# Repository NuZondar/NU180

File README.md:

# NU180
A reverse-engineered replacement for the U180 hybrid in the Hewlett-Packard / Agilent / Keysight 3458A DVM. 

Briefly, the custom "U180" hybrid in the 3458A is infamously prone to excessive drifting or outright failure, but is absolutely unavailable. NU180 is a drop-in replacement for that hybrid. Still under development, its performance falls slightly short of an original U180, e.g. noise performance is ~20-30% higher than spec, but it thus provides at least 8 digits conversion (within 2x of 8.5 digits), which is infinitely better than a dead or dying machine! 

Some notes:

The new Version 1.1 files are denoted "v11" in their names. 

The layout requires 6 layers. Choose a thin stack-up - that is, thinner core layers - if available. 

Choose the best resistors you can find, especially for their TCR (temperature coefficient of resistance). In particular, the use of low TCR bulk-foil resistors for at least the 50k and most-critical 80k's are recommended for best temperature stability. 

The footprints for the critical 80k's allow choosing either large 2512 surface-mount resistors, or else through-hole resistors (same for the 50k). These are intended for builders who are using bulk-foil resistors (80k's only come in 2512 size). You can edit the files to delete the unused footprints or else leave them in place. Another option for the 50k and 80k resistors is to edit the files to substitute a small array of series or parallel resistors. There's room for up to 4 each, e.g. 4x 20k in series for the 80k's, etc. 

You also have the option of using voltage regulation on the flip-flop and inverter (recommended), or else using unregulated 5V, chosen via jumpers. The schematic shows parts suitable for 3.3V operation, but other parts may allow operation down to 2.5V. The lower-voltage regulation should help keep noise down. 

The 100k resistors to ground are optional and need not be included unless some problem is seen. 

Debugging: The 3458A is a very sensitive instrument that can be quite fussy about error codes. At least in earlier versions, builders have sometimes found that changing the value of the series resistors (the 100 Ohm ones) up or down, e.g. to 33 or 220 Ohms, can help. Usually, only the four switch control lines associated with the 80k resistors (S5, S7, S9, S11) might need tuning. Another hack that has sometimes helped is adding a small capacitor (5-10 pF) in parallel with the R140 resistor on the A3 board.

There is extensive discussion of this project in the metrology section of EEVblog. Many people contributed their knowledge and experience towards its success, including MiDi, DB4UCH, wanghar, Kleinstein and others. 

Good luck!

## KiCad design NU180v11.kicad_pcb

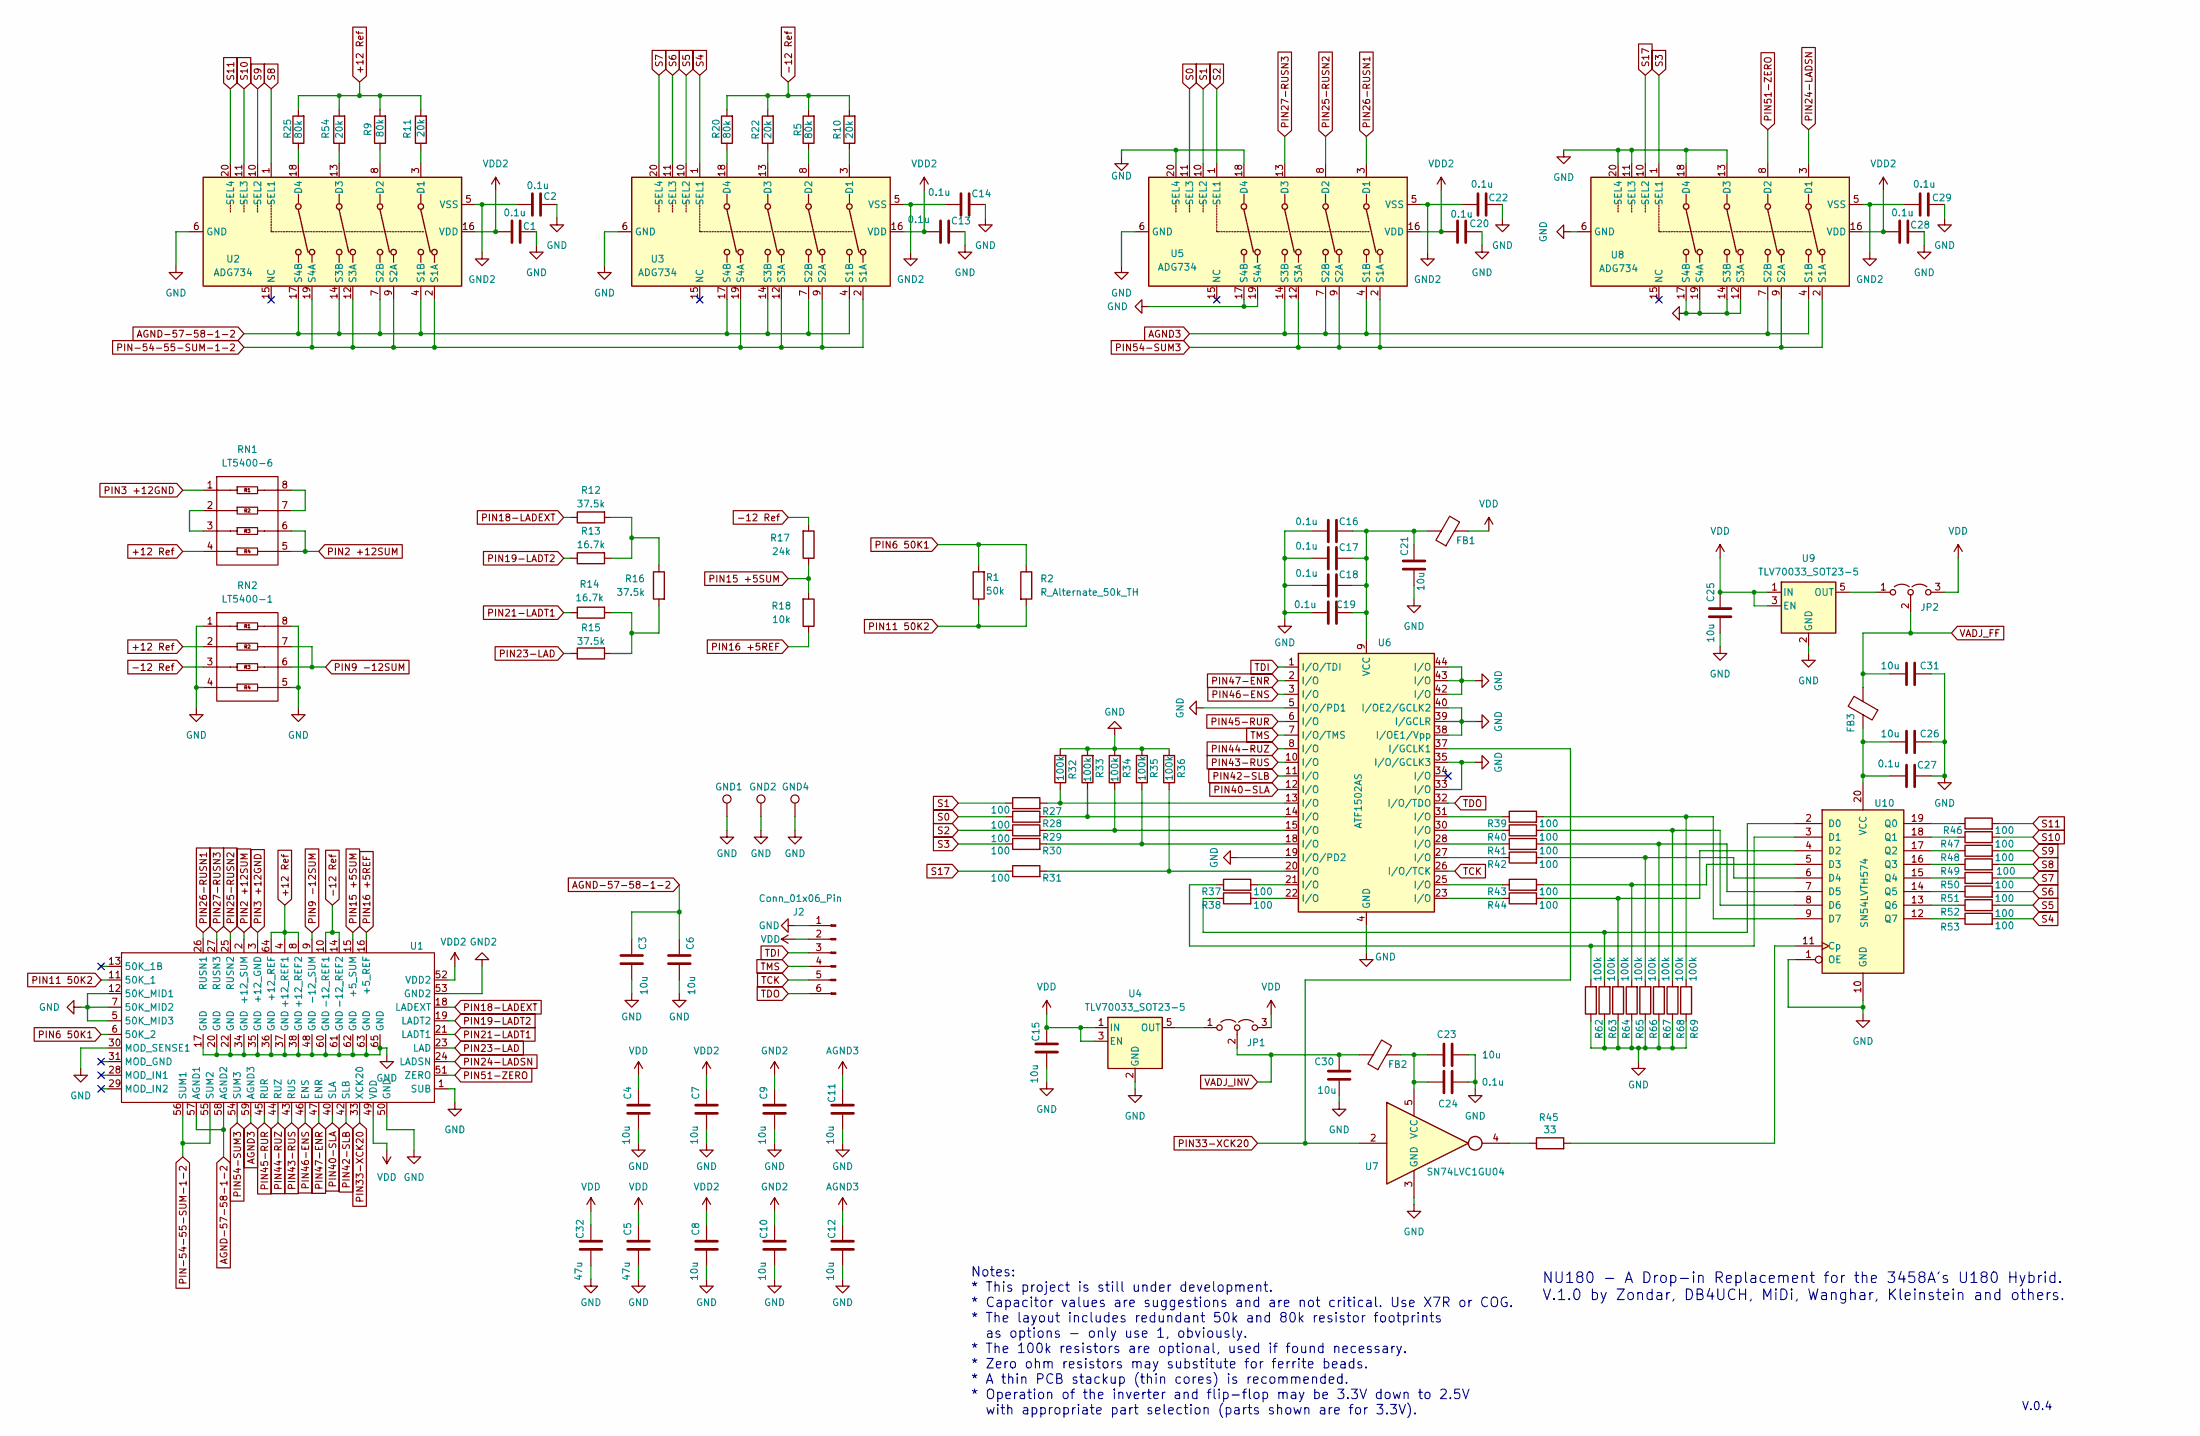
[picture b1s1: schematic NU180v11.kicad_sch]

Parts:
C1, C2, C13, C14, C16, C17, C18, C19, C20, C22, C24, C27, C28, C29: 0.1u; C_0603_1608Metric
C3, C4, C6, C7, C8, C9, C10, C11, C12, C15, C21, C23, C25, C26, C30, C31: 10u; C_0805_2012Metric_Pad1.18x1.45mm_HandSolder
C5, C32: 47u; C_1206_3216Metric
FB1, FB2, FB3: Ferrite Bead or Short; C_0603_1608Metric
GND1, GND2, GND4: TestPoint; PinHeader_1x01_P2.54mm_Vertical
J2: Conn_01x06_Pin; PinHeader_1x06_P2.54mm_Vertical
JP1, JP2: Jumper_3_Open; SolderJumper-3_P2.0mm_Open_TrianglePad1.0x1.5mm
R1: 50k; R_2010_5025Metric
R2: R_Alternate_50k_TH; R_Axial_DIN0204_L3.6mm_D1.6mm_P5.08mm_Horizontal
R5, R9, R20, R25: 80k; R_2512_6332Metric
R10, R11, R22, R54: 20k; R_1206_3216Metric
R12, R15, R16: 37.5k; R_0805_2012Metric
R13, R14: 16.7k; R_0805_2012Metric
R17: 24k; R_1206_3216Metric
R18: 10k; R_1206_3216Metric
R27, R28, R29, R30, R31, R37, R38, R39, R40, R41, R42, R43, R44, R46, R47, R48, R49, R50, R51, R52, R53: 100; R_0603_1608Metric
R32, R33, R34, R35, R36, R62, R63, R64, R65, R66, R67, R68, R69: 100k; R_0603_1608Metric
R45: 33; R_0603_1608Metric
RN1: LT5400-6; MSOP-8-1EP_3x3mm_P0.65mm_EP1.68x1.88mm
RN2: LT5400-1; MSOP-8-1EP_3x3mm_P0.65mm_EP1.68x1.88mm
U1: U180PINS
U2, U3, U5, U8: ADG734; TSSOP-20_4.4x6.5mm_P0.65mm
U4, U9: TLV70033_SOT23-5; SOT-23-5
U6: ATF1502AS; TQFP-44_10x10mm_P0.8mm
U7: SN74LVC1GU04; SOT-353_SC-70-5
U10: SN54LVTH574; TSSOP-20_4.4x6.5mm_P0.65mm

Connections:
+12 Ref: R9.2, R11.2, R25.2, R54.2, RN1.4, RN2.2, U1.4 (+12_REF1), U1.8 (+12_REF2), U1.64 (+12_REF)
-12 Ref: R5.2, R10.2, R17.2, R20.2, R22.2, RN2.3, U1.10 (-12_REF1), U1.14 (-12_REF2)
AGND3: C11.2, C12.2, U1.59 (AGND3), U5.4 (S1B), U5.7 (S2B), U5.14 (S3B), U8.4 (S1B), U8.7 (S2B)
AGND-57-58-1-2: C3.2, C6.2, U1.57 (AGND1), U1.58 (AGND2), U2.4 (S1B), U2.7 (S2B), U2.14 (S3B), U2.17 (S4B), U3.4 (S1B), U3.7 (S2B), U3.14 (S3B), U3.17 (S4B)
GND: C1.2, C2.2, C3.1, C4.1, C5.1, C6.1, C7.1, C8.1, C9.1, C10.1, C11.1, C12.1, C13.2, C14.2, C15.1, C16.1, C17.1, C18.1, C19.1, C20.2, C21.1, C22.2, C23.2, C24.2, C25.1, C26.2, C27.2, C28.2, C29.2, C30.1, C31.2, C32.1, GND1.1, GND2.1, GND4.1, J2.1, R32.2, R33.2, R34.2, R35.2, R36.2, R62.1, R63.1, R64.1, R65.1, R66.1, R67.1, R68.1, R69.1, RN2.1, RN2.4, RN2.5, RN2.8, U1.1 (SUB), U1.5 (50K_MID3), U1.7 (50K_MID2), U1.12 (50K_MID1), U1.17 (GND), U1.20 (GND), U1.22 (GND), U1.30 (MOD_SENSE1), U1.34 (GND), U1.35 (GND), U1.36 (GND), U1.37 (GND), U1.38 (GND), U1.48 (GND), U1.50 (GND), U1.60 (GND), U1.61 (GND), U1.62 (GND), U1.63 (GND), U1.65 (GND), U2.6 (GND), U3.6 (GND), U4.2 (GND), U5.6 (GND), U5.17 (S4B), U5.18 (D4), U5.19 (S4A), U5.20 (SEL4), U6.4 (GND), U6.5 (I/O/PD1), U6.16 (GND), U6.19 (I/O/PD2), U6.24 (GND), U6.33 (I/O), U6.35 (I/O/GCLK3), U6.36 (GND), U6.38 (I/OE1/Vpp), U6.39 (I/GCLR), U6.40 (I/OE2/GCLK2), U6.42 (I/O), U6.43 (I/O), U6.44 (I/O), U7.3 (GND), U8.6 (GND), U8.11 (SEL3), U8.12 (S3A), U8.13 (D3), U8.14 (S3B), U8.17 (S4B), U8.18 (D4), U8.19 (S4A), U8.20 (SEL4), U9.2 (GND), U10.1 (OE), U10.10 (GND); also elsewhere on the board
GND2: C2.1, C9.2, C10.2, C14.1, C22.1, C29.1, U1.53 (GND2), U2.5 (VSS), U3.5 (VSS), U5.5 (VSS), U8.5 (VSS)
unnamed: C16.2, C17.2, C18.2, C19.2, C21.2, FB1.1, U6.9 (VCC), U6.17 (VCC), U6.29 (VCC), U6.41 (VCC)
unnamed: JP1.1 (A), U4.5 (OUT)
unnamed: JP2.1 (A), U9.5 (OUT)
unnamed: R12.2, R13.2, R16.1
unnamed: R14.2, R15.2, R16.2
unnamed: R27.2, R32.1, U6.13 (I/O)
unnamed: R28.2, R33.1, U6.14 (I/O)
unnamed: R29.2, R34.1, U6.15 (I/O)
unnamed: R30.2, R35.1, U6.18 (I/O)
unnamed: R31.2, R36.1, U6.20 (I/O)
unnamed: R37.2, U6.21 (I/O)
unnamed: R38.2, U6.22 (I/O)
unnamed: R39.1, U6.31 (I/O)
unnamed: R40.1, U6.30 (I/O)
unnamed: R41.1, U6.28 (I/O)
unnamed: R42.1, U6.27 (I/O)
unnamed: R43.1, U6.25 (I/O)
unnamed: R44.1, U6.23 (I/O)
unnamed: R45.1, U7.4
unnamed: RN1.2, RN1.3
unnamed: RN1.7, RN1.8
unnamed: R11.1, U2.3 (D1)
unnamed: R9.1, U2.8 (D2)
unnamed: R54.1, U2.13 (D3)
unnamed: R25.1, U2.18 (D4)
unnamed: R10.1, U3.3 (D1)
unnamed: R5.1, U3.8 (D2)
unnamed: R22.1, U3.13 (D3)
unnamed: R20.1, U3.18 (D4)
unnamed: C23.1, C24.1, FB2.2, U7.5 (VCC)
unnamed: R45.2, U10.11 (Cp)
unnamed: R38.1, R63.2, U10.2 (D0)
unnamed: R37.1, R62.2, U10.3 (D1)
unnamed: R44.2, R64.2, U10.4 (D2)
unnamed: R43.2, R65.2, U10.5 (D3)
unnamed: R42.2, R66.2, U10.6 (D4)
unnamed: R41.2, R67.2, U10.7 (D5)
unnamed: R40.2, R68.2, U10.8 (D6)
unnamed: R39.2, R69.2, U10.9 (D7)
unnamed: R46.1, U10.19 (Q0)
unnamed: R47.1, U10.18 (Q1)
unnamed: R48.1, U10.17 (Q2)
unnamed: R49.1, U10.16 (Q3)
unnamed: R50.1, U10.15 (Q4)
unnamed: R51.1, U10.14 (Q5)
unnamed: R52.1, U10.13 (Q6)
unnamed: R53.1, U10.12 (Q7)
unnamed: C26.1, C27.1, FB3.1, U10.20 (VCC)
PIN2 +12SUM: RN1.5, RN1.6, U1.2 (+12_SUM)
PIN3 +12GND: RN1.1, U1.3 (+12_GND)
PIN6 50K1: R1.2, R2.1, U1.6 (50K_2)
PIN9 -12SUM: RN2.6, RN2.7, U1.9 (-12_SUM)
PIN11 50K2: R1.1, R2.2, U1.11 (50K_1)
PIN15 +5SUM: R17.1, R18.2, U1.15 (+5_SUM)
PIN16 +5REF: R18.1, U1.16 (+5_REF)
PIN18-LADEXT: R12.1, U1.18 (LADEXT)
PIN19-LADT2: R13.1, U1.19 (LADT2)
PIN21-LADT1: R14.1, U1.21 (LADT1)
PIN23-LAD: R15.1, U1.23 (LAD)
PIN24-LADSN: U1.24 (LADSN), U8.3 (D1)
PIN25-RUSN2: U1.25 (RUSN2), U5.8 (D2)
PIN26-RUSN1: U1.26 (RUSN1), U5.3 (D1)
PIN27-RUSN3: U1.27 (RUSN3), U5.13 (D3)
PIN33-XCK20: U1.33 (XCK20), U6.37 (I/GCLK1), U7.2
PIN40-SLA: U1.40 (SLA), U6.12 (I/O)
PIN42-SLB: U1.42 (SLB), U6.11 (I/O)
PIN43-RUS: U1.43 (RUS), U6.10 (I/O)
PIN44-RUZ: U1.44 (RUZ), U6.8 (I/O)
PIN45-RUR: U1.45 (RUR), U6.6 (I/O)
PIN46-ENS: U1.46 (ENS), U6.3 (I/O)
PIN47-ENR: U1.47 (ENR), U6.2 (I/O)
PIN51-ZERO: U1.51 (ZERO), U8.8 (D2)
PIN54-SUM3: U1.54 (SUM3), U5.2 (S1A), U5.9 (S2A), U5.12 (S3A), U8.2 (S1A), U8.9 (S2A)
PIN-54-55-SUM-1-2: U1.55 (SUM2), U1.56 (SUM1), U2.2 (S1A), U2.9 (S2A), U2.12 (S3A), U2.19 (S4A), U3.2 (S1A), U3.9 (S2A), U3.12 (S3A), U3.19 (S4A)
S0: R28.1, U5.11 (SEL3)
S1: R27.1, U5.10 (SEL2)
S2: R29.1, U5.1 (SEL1)
S3: R30.1, U8.1 (SEL1)
S4: R53.2, U3.1 (SEL1)
S5: R52.2, U3.10 (SEL2)
S6: R51.2, U3.11 (SEL3)
S7: R50.2, U3.20 (SEL4)
S8: R49.2, U2.1 (SEL1)
S9: R48.2, U2.10 (SEL2)
S10: R47.2, U2.11 (SEL3)
S11: R46.2, U2.20 (SEL4)
S17: R31.1, U8.10 (SEL2)
TCK: J2.5, U6.26 (I/O/TCK)
TDI: J2.3, U6.1 (I/O/TDI)
TDO: J2.6, U6.32 (I/O/TDO)
TMS: J2.4, U6.7 (I/O/TMS)
VADJ_FF: C31.1, FB3.2, JP2.2 (C)
VADJ_INV: C30.2, FB2.1, JP1.2 (C)
VDD: C4.2, C5.2, C15.2, C25.2, C32.2, FB1.2, J2.2, JP1.3 (B), JP2.3 (B), U1.49 (VDD), U4.1 (IN), U4.3 (EN), U9.1 (IN), U9.3 (EN)
VDD2: C1.1, C7.2, C8.2, C13.1, C20.1, C28.1, U1.52 (VDD2), U2.16 (VDD), U3.16 (VDD), U5.16 (VDD), U8.16 (VDD)

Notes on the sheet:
V.0.4
Notes: * This project is still under development. * Capacitor values are suggestions and are not critical. Use X7R or COG. * The layout includes redundant 50k and 80k resistor footprints as options - only use 1, obviously. * The 100k resistors are optional, used if found necessary. * Zero ohm resis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
NU180 - A Drop-in Replacement for the 3458A's U180 Hybrid. V.1.0 by Zondar, DB4UCH, MiDi, Wanghar, Kleinstein and others.

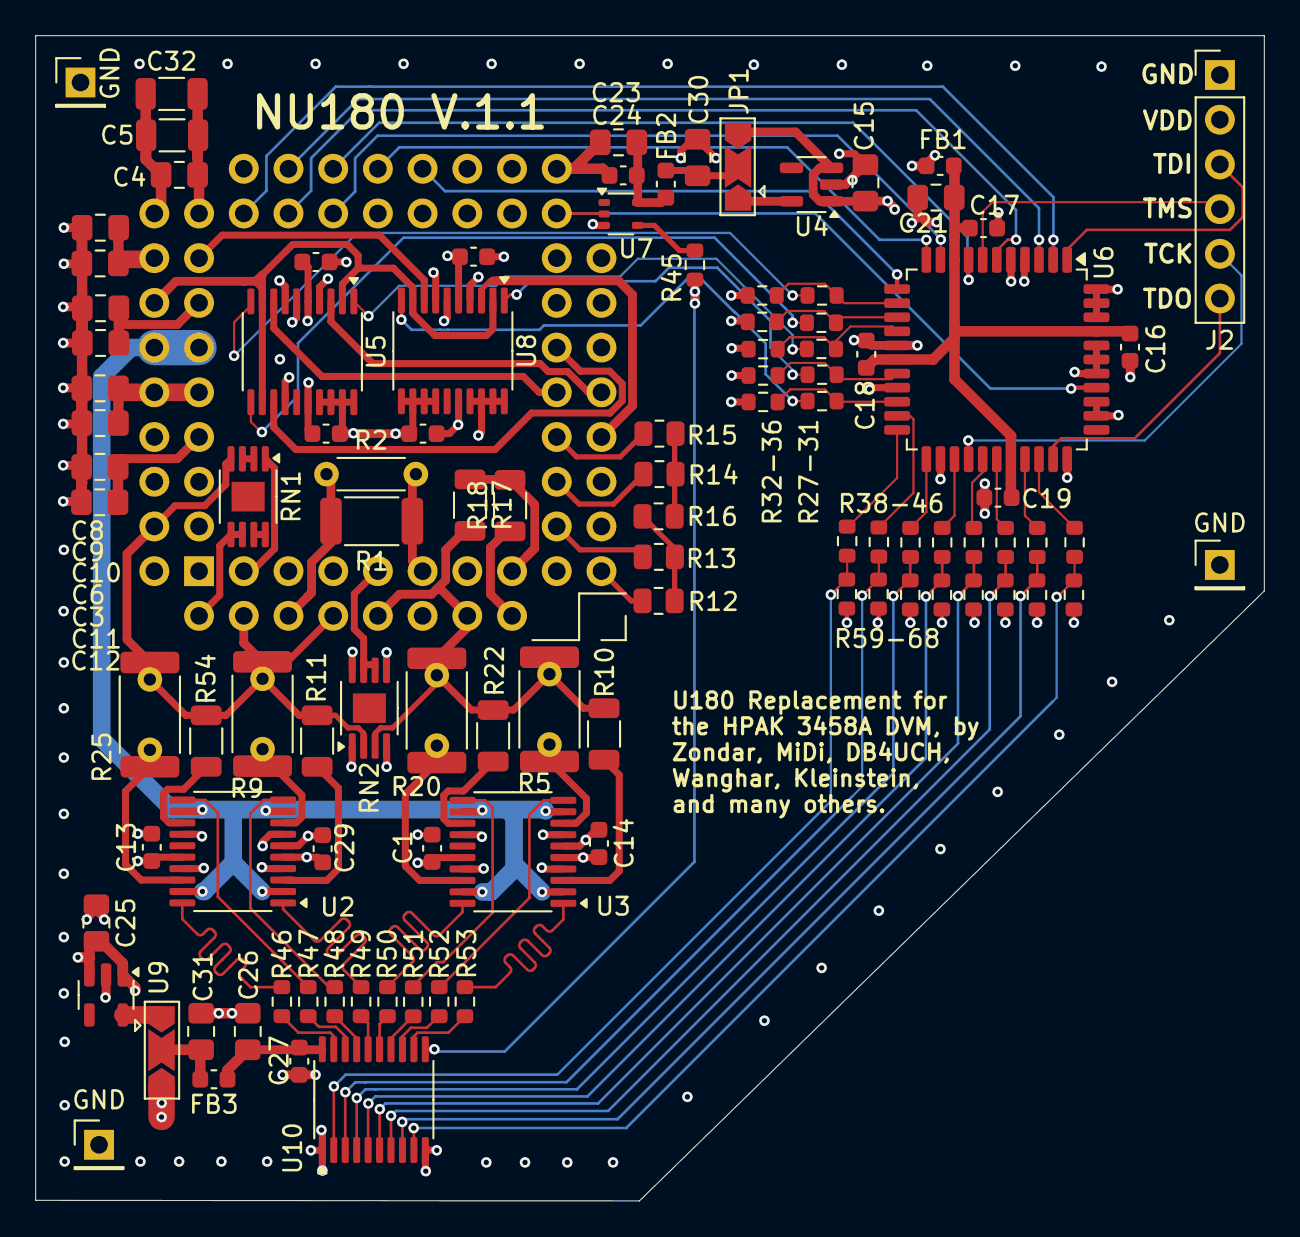
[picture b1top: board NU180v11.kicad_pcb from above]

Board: 6 copper layers, 69.8 x 66.2 mm, 105 parts (0 on the bottom side), 101 nets.

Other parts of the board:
GND: TestPoint; PinHeader_1x01_P2.54mm_Vertical
GND#2: TestPoint; PinHeader_1x01_P2.54mm_Vertical

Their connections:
GND: GND.1, GND#2.1; also elsewhere on the board

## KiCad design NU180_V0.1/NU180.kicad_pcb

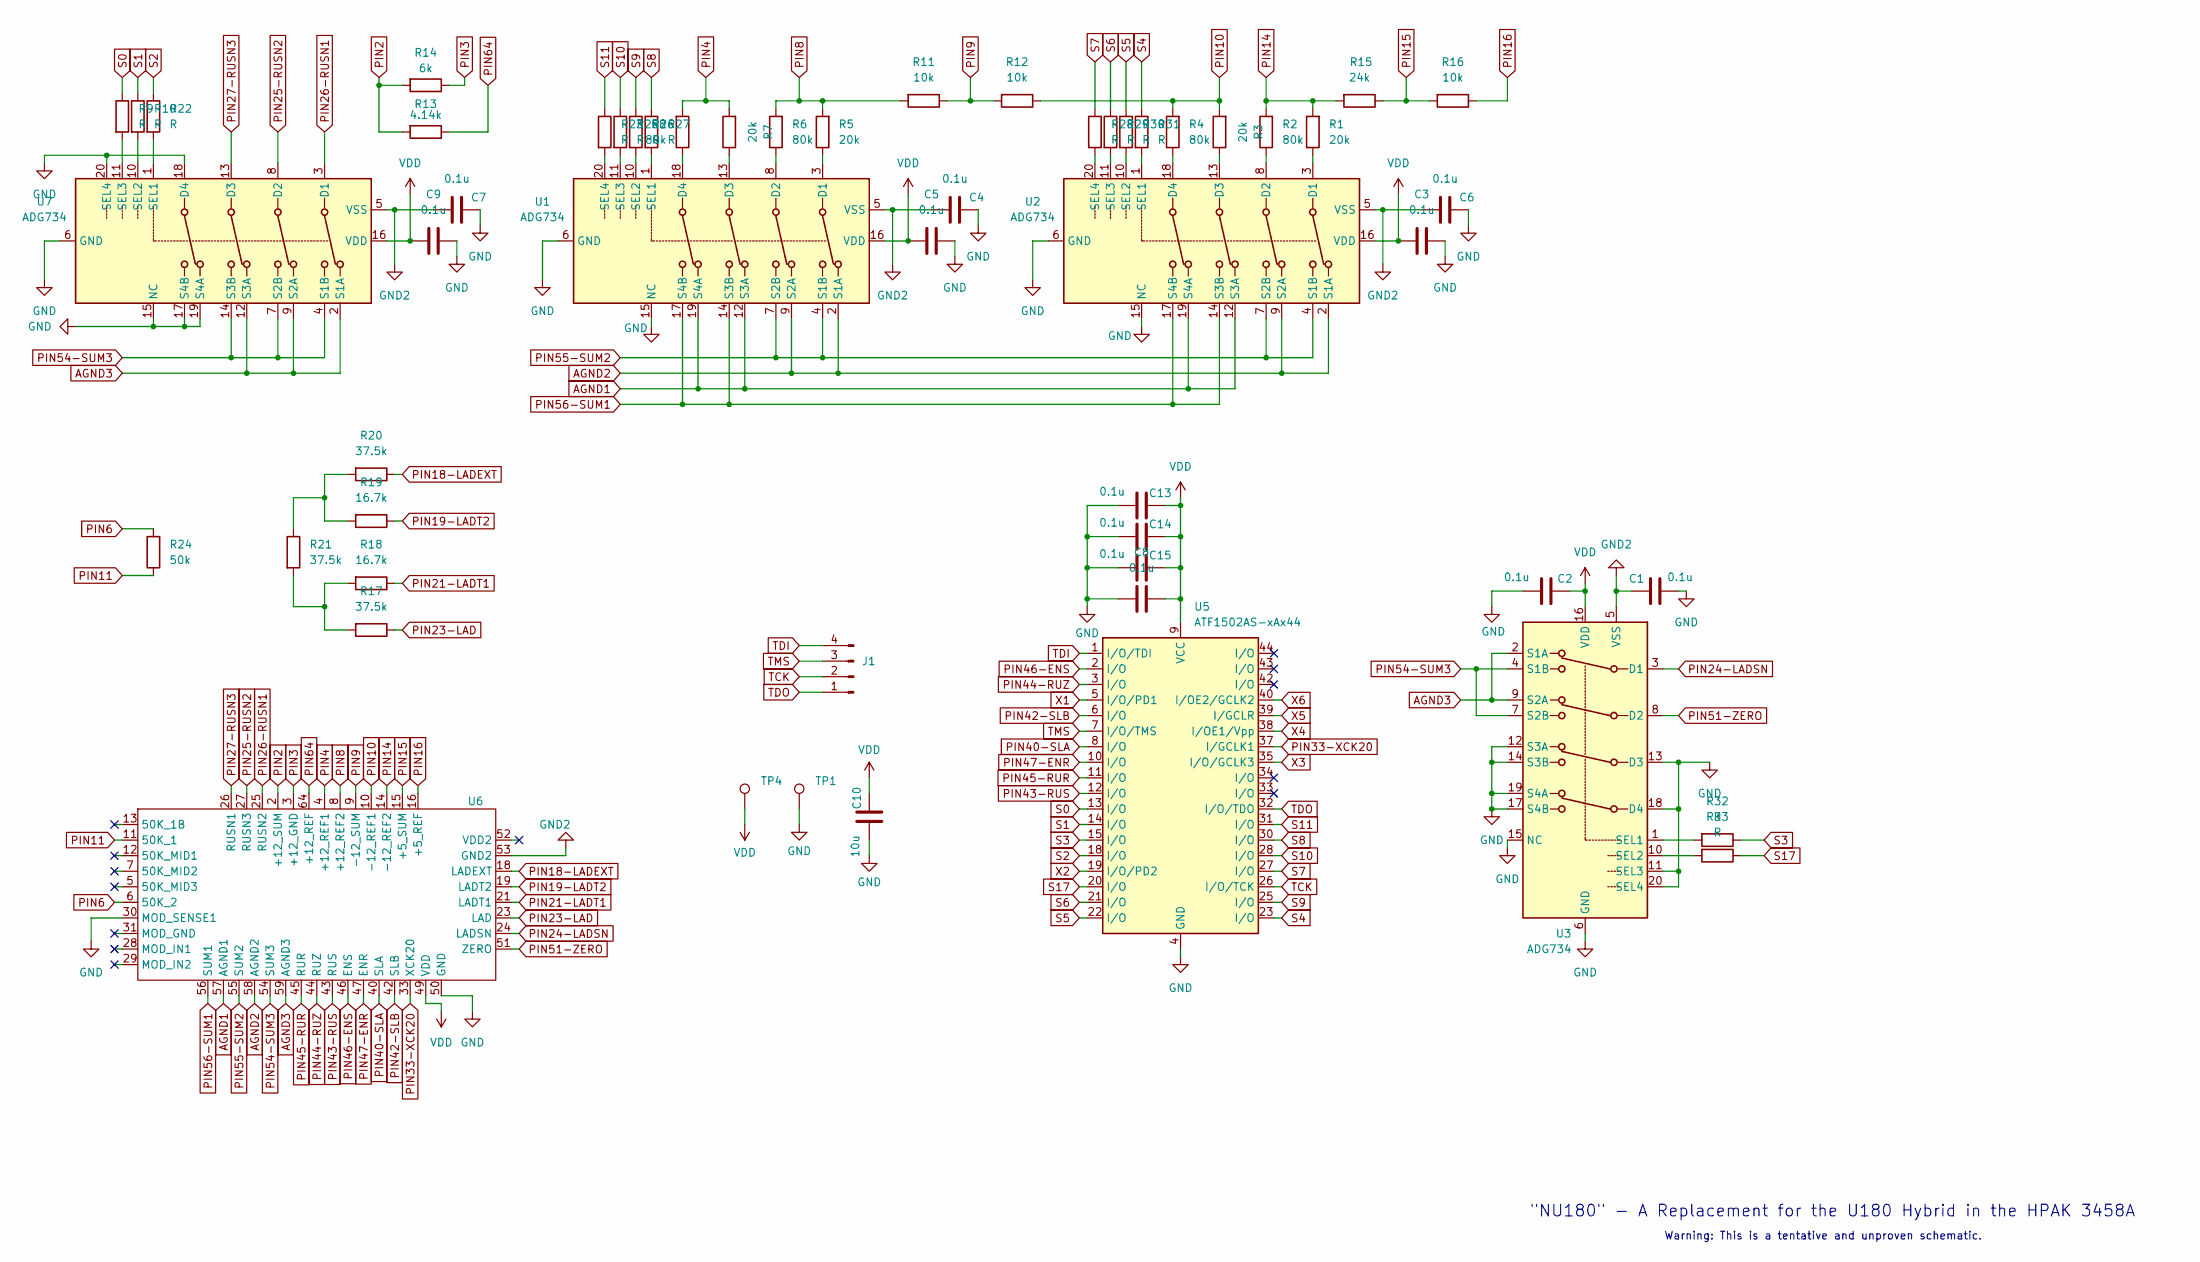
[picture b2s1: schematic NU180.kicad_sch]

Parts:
C1, C2, C3, C4, C5, C6, C7, C8, C9, C13, C14, C15: 0.1u; C_0603_1608Metric_Pad1.08x0.95mm_HandSolder
C10: 10u; C_0805_2012Metric_Pad1.18x1.45mm_HandSolder
J1: Conn_01x04_Pin; PinHeader_1x04_P2.54mm_Vertical
R1, R3, R5, R7: 20k; R_1206_3216Metric
R2, R4, R6, R8: 80k; R_2512_6332Metric
R9, R10, R22, R23, R25, R26, R27, R28, R29, R30, R31, R32, R33: R; C_0603_1608Metric_Pad1.08x0.95mm_HandSolder
R11, R12, R16: 10k; R_1206_3216Metric
R13: 4.14k; R_1206_3216Metric
R14: 6k; R_1206_3216Metric
R15: 24k; R_1206_3216Metric
R17, R20, R21: 37.5k; R_0805_2012Metric_Pad1.20x1.40mm_HandSolder
R18, R19: 16.7k; R_0805_2012Metric_Pad1.20x1.40mm_HandSolder
R24: 50k; R_2512_6332Metric
TP1, TP4: TestPoint; PinHeader_1x01_P2.54mm_Vertical
U1, U2, U3, U7: ADG734; TSSOP-20_4.4x6.5mm_P0.65mm
U5: ATF1502AS-xAx44; TQFP-44_10x10mm_P0.8mm
U6: U180PINS

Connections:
AGND1: U1.12 (S3A), U1.19 (S4A), U2.12 (S3A), U2.19 (S4A), U6.57 (AGND1)
AGND2: U1.2 (S1A), U1.9 (S2A), U2.2 (S1A), U2.9 (S2A), U6.58 (AGND2)
AGND3: U3.2 (S1A), U3.9 (S2A), U6.59 (AGND3), U7.2 (S1A), U7.9 (S2A), U7.12 (S3A)
GND: C1.1, C2.1, C3.1, C4.1, C5.1, C6.1, C7.1, C8.1, C9.1, C10.1, C13.1, C14.1, C15.1, TP1.1, U1.6 (GND), U1.15 (NC), U2.6 (GND), U2.15 (NC), U3.6 (GND), U3.11 (SEL3), U3.12 (S3A), U3.13 (D3), U3.14 (S3B), U3.15 (NC), U3.17 (S4B), U3.18 (D4), U3.19 (S4A), U3.20 (SEL4), U5.4 (GND), U5.16 (GND), U5.24 (GND), U5.36 (GND), U6.30 (MOD_SENSE1), U6.50 (GND), U7.6 (GND), U7.15 (NC), U7.17 (S4B), U7.18 (D4), U7.19 (S4A), U7.20 (SEL4)
GND2: C1.2, C4.2, C6.2, C7.2, U1.5 (VSS), U2.5 (VSS), U3.5 (VSS), U6.53 (GND2), U7.5 (VSS)
unnamed: R17.2, R18.2, R21.2
unnamed: R19.2, R20.2, R21.1
unnamed: R5.1, U1.3 (D1)
unnamed: R6.1, U1.8 (D2)
unnamed: R7.1, U1.13 (D3)
unnamed: R8.1, U1.18 (D4)
unnamed: R27.2, U1.1 (SEL1)
unnamed: R26.2, U1.10 (SEL2)
unnamed: R25.2, U1.11 (SEL3)
unnamed: R23.2, U1.20 (SEL4)
unnamed: R1.1, U2.3 (D1)
unnamed: R2.1, U2.8 (D2)
unnamed: R3.1, U2.13 (D3)
unnamed: R4.1, U2.18 (D4)
unnamed: R31.2, U2.1 (SEL1)
unnamed: R30.2, U2.10 (SEL2)
unnamed: R29.2, U2.11 (SEL3)
unnamed: R28.2, U2.20 (SEL4)
unnamed: R32.2, U3.1 (SEL1)
unnamed: R33.2, U3.10 (SEL2)
unnamed: R22.2, U7.1 (SEL1)
unnamed: R10.2, U7.10 (SEL2)
unnamed: R9.2, U7.11 (SEL3)
PIN2: R13.2, R14.2, U6.2 (+12_SUM)
PIN3: R14.1, U6.3 (+12_GND)
PIN4: R7.2, R8.2, U6.4 (+12_REF1)
PIN6: R24.2, U6.6 (50K_2)
PIN8: R5.2, R6.2, R11.2, U6.8 (+12_REF2)
PIN9: R11.1, R12.2, U6.9 (-12_SUM)
PIN10: R3.2, R4.2, R12.1, U6.10 (-12_REF1)
PIN11: R24.1, U6.11 (50K_1)
PIN14: R1.2, R2.2, R15.2, U6.14 (-12_REF2)
PIN15: R15.1, R16.2, U6.15 (+5_SUM)
PIN16: R16.1, U6.16 (+5_REF)
PIN18-LADEXT: R20.1, U6.18 (LADEXT)
PIN19-LADT2: R19.1, U6.19 (LADT2)
PIN21-LADT1: R18.1, U6.21 (LADT1)
PIN23-LAD: R17.1, U6.23 (LAD)
PIN24-LADSN: U3.3 (D1), U6.24 (LADSN)
PIN25-RUSN2: U6.27 (RUSN3), U7.8 (D2)
PIN26-RUSN1: U6.25 (RUSN2), U7.3 (D1)
PIN27-RUSN3: U6.26 (RUSN1), U7.13 (D3)
PIN33-XCK20: U5.37 (I/GCLK1), U6.33 (XCK20)
PIN40-SLA: U5.8 (I/O), U6.40 (SLA)
PIN42-SLB: U5.6 (I/O), U6.42 (SLB)
PIN43-RUS: U5.12 (I/O), U6.43 (RUS)
PIN44-RUZ: U5.3 (I/O), U6.44 (RUZ)
PIN45-RUR: U5.11 (I/O), U6.45 (RUR)
PIN46-ENS: U5.2 (I/O), U6.46 (ENS)
PIN47-ENR: U5.10 (I/O), U6.47 (ENR)
PIN51-ZERO: U3.8 (D2), U6.51 (ZERO)
PIN54-SUM3: U3.4 (S1B), U3.7 (S2B), U6.54 (SUM3), U7.4 (S1B), U7.7 (S2B), U7.14 (S3B)
PIN55-SUM2: U1.4 (S1B), U1.7 (S2B), U2.4 (S1B), U2.7 (S2B), U6.55 (SUM2)
PIN56-SUM1: U1.14 (S3B), U1.17 (S4B), U2.14 (S3B), U2.17 (S4B), U6.56 (SUM1)
PIN64: R13.1, U6.64 (+12_REF)
S0: R9.1, U5.13 (I/O)
S1: R10.1, U5.14 (I/O)
S2: R22.1, U5.18 (I/O)
S3: R32.1, U5.15 (I/O)
S4: R31.1, U5.23 (I/O)
S5: R30.1, U5.22 (I/O)
S6: R29.1, U5.21 (I/O)
S7: R28.1, U5.27 (I/O)
S8: R27.1, U5.30 (I/O)
S9: R26.1, U5.25 (I/O)
S10: R25.1, U5.28 (I/O)
S11: R23.1, U5.31 (I/O)
S17: R33.1, U5.20 (I/O)
TCK: J1.2, U5.26 (I/O/TCK)
TDI: J1.4, U5.1 (I/O/TDI)
TDO: J1.1, U5.32 (I/O/TDO)
TMS: J1.3, U5.7 (I/O/TMS)
VDD: C2.2, C3.2, C5.2, C8.2, C9.2, C10.2, C13.2, C14.2, C15.2, TP4.1, U1.16 (VDD), U2.16 (VDD), U3.16 (VDD), U5.9 (VCC), U5.17 (VCC), U5.29 (VCC), U5.41 (VCC), U6.49 (VDD), U7.16 (VDD)
X1: U5.5 (I/O/PD1)
X2: U5.19 (I/O/PD2)
X3: U5.35 (I/O/GCLK3)
X4: U5.38 (I/OE1/Vpp)
X5: U5.39 (I/GCLR)
X6: U5.40 (I/OE2/GCLK2)

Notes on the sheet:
Warning: This is a tentative and unproven schematic.
"NU180" - A Replacement for the U180 Hybrid in the HPAK 3458A

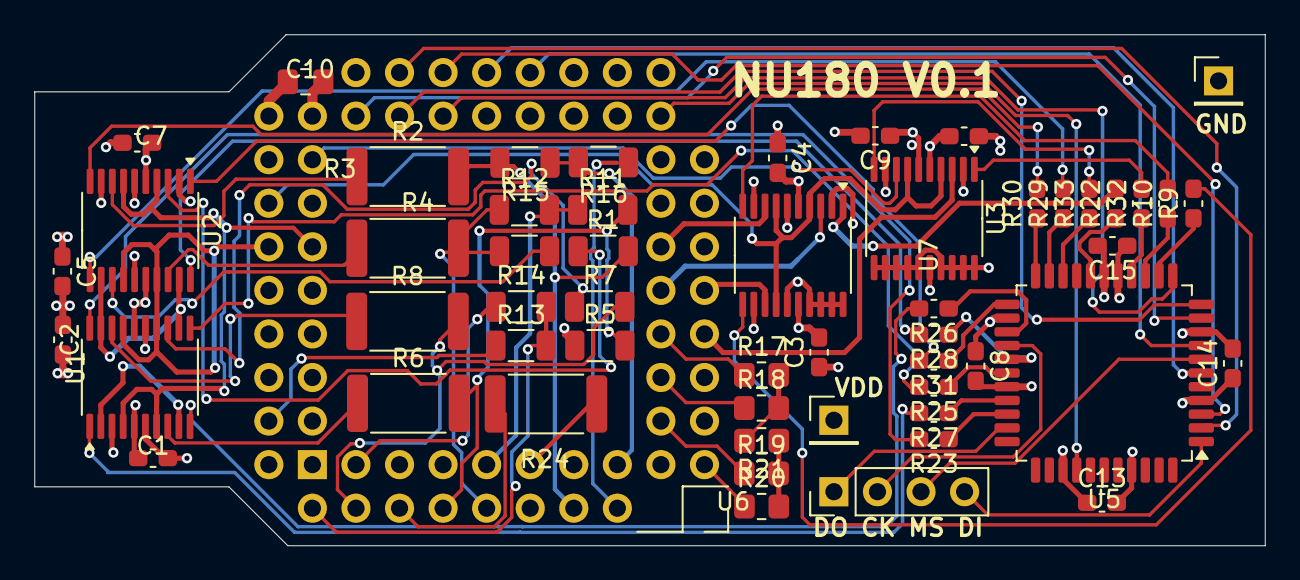
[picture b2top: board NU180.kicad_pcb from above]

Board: 6 copper layers, 71.7 x 29.8 mm, 55 parts (0 on the bottom side), 78 nets.

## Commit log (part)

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2025-09-24 Add files via upload
    “NU180” is a project to create a reverse-engineered drop-in replacement for the U180 hybrid in the Hewlett-Packard / Agilent / Keysight 3458A 8.5 digit DVM.
    The U180 hybrid was designed by HP in the 1980’s. In one package, it includes a custom current-steering chip and a custom resistor array. As many with an 3458A knows all too painfully, its “A3” ADC b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
